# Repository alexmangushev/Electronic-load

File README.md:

# Electronic-load
The project is an electronic load together with a battery capacity meter. The STM32 microcontroller acts as a calculating module.
If you have to use this project, name the folder of project "F103C8_Electronic_load"

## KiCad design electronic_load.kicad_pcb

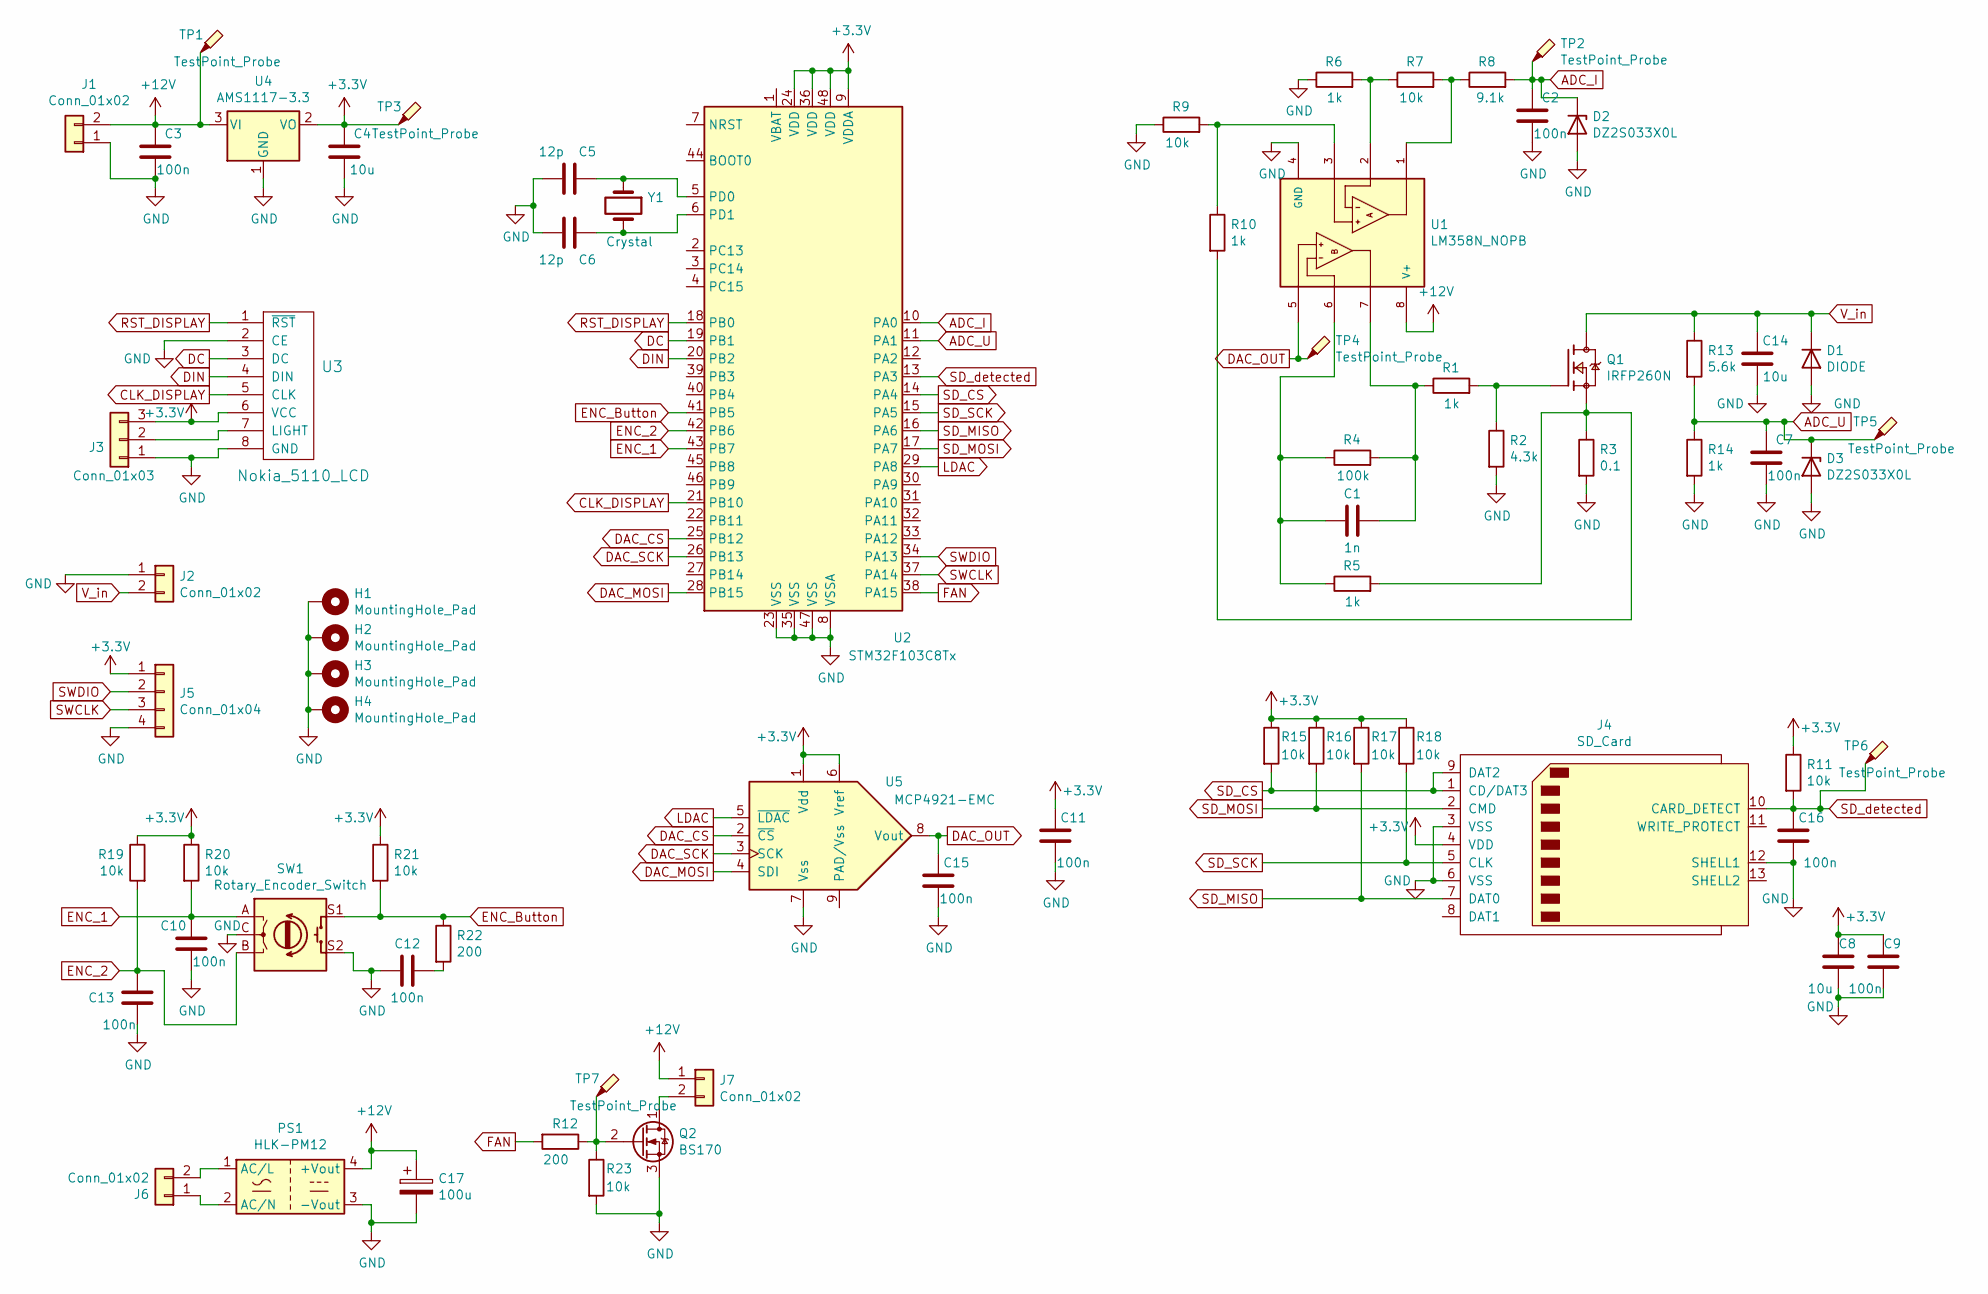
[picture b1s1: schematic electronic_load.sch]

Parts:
C1: 1n; C_1206_3216Metric
C2, C3, C7, C9, C10, C11, C12, C13, C15, C16: 100n; C_1206_3216Metric
C4, C8, C14: 10u; C_1206_3216Metric
C5, C6: 12p; C_1206_3216Metric
C17: 100u; CP_Radial_D7.5mm_P2.50mm
D1: DIODE; D_SMA
D2, D3: DZ2S033X0L; D_SOD-523
H1, H2, H3, H4: MountingHole_Pad; MountingHole_3.2mm_M3_Pad_Via
J1, J6: Conn_01x02; PinHeader_1x02_P2.54mm_Vertical
J2: Conn_01x02; AMASS_XT30UPB-F_1x02_P5.0mm_Vertical
J3: Conn_01x03; PinHeader_1x03_P2.54mm_Vertical
J4: SD_Card; SD_TE_2041021
J5: Conn_01x04; PinHeader_1x04_P2.54mm_Vertical
J7: Conn_01x02; PinSocket_1x02_P2.54mm_Vertical
PS1: HLK-PM12; Hi_Link_12_5
Q1: IRFP260N; TO-247-3_Vertical; PARTREV 08/18/10
Q2: BS170; TO-92_Inline
R1, R5, R6, R10, R14: 1k; R_1206_3216Metric
R2: 4.3k; R_1206_3216Metric
R3: 0.1; R_Axial_Power_L25.0mm_W9.0mm_P27.94mm
R4: 100k; R_1206_3216Metric
R7, R9, R11, R15, R16, R17, R18, R19, R20, R21, R23: 10k; R_1206_3216Metric
R8: 9.1k; R_1206_3216Metric
R12, R22: 200; R_1206_3216Metric
R13: 5.6k; R_1206_3216Metric
SW1: Rotary_Encoder_Switch; RotaryEncoder_Alps_EC11E-Switch_Vertical_H20mm
TP1, TP2, TP3, TP4, TP5, TP6, TP7: TestPoint_Probe; TestPoint_Pad_1.0x1.0mm
U1: LM358N_NOPB; SOIC-8_3.9x4.9mm_P1.27mm
U2: STM32F103C8Tx; LQFP-48_7x7mm_P0.5mm
U3: Nokia_5110_LCD; PinHeader_1x08_P2.54mm_Vertical
U4: AMS1117-3.3; SOT-223-3_TabPin2
U5: MCP4921-EMC; SOIC-8_3.9x4.9mm_P1.27mm
Y1: Crystal; Crystal_SMD_5032-2Pin_5.0x3.2mm

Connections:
+3V3: C4.1, C8.1, C9.1, C11.1, J3.3, J4.4 (VDD), J5.1, R11.1, R15.1, R16.1, R17.1, R18.1, R19.1, R20.1, R21.1, TP3.1, U2.9 (VDDA), U2.24 (VDD), U2.36 (VDD), U2.48 (VDD), U3.6 (VCC), U4.2 (VO), U5.1 (Vdd), U5.6 (Vref)
+12V: C3.1, C17.1, J1.2, J7.1, PS1.4 (+Vout), TP1.1, U1.8 (V+), U4.3 (VI)
ADC_I: C2.1, D2.1 (K), R8.2, TP2.1, U2.10 (PA0)
ADC_U: C7.1, D3.1 (K), R13.2, R14.1, TP5.1, U2.11 (PA1)
CLK_DISPLAY: U2.21 (PB10), U3.5 (CLK)
DAC_CS: U2.25 (PB12), U5.2 (~CS)
DAC_MOSI: U2.28 (PB15), U5.4 (SDI)
DAC_OUT: C15.1, TP4.1, U1.5, U5.8 (Vout)
DAC_SCK: U2.26 (PB13), U5.3 (SCK)
DC: U2.19 (PB1), U3.3 (DC)
DIN: U2.20 (PB2), U3.4 (DIN)
ENC_1: C10.1, R20.2, SW1.A, U2.43 (PB7)
ENC_2: C13.1, R19.2, SW1.B, U2.42 (PB6)
ENC_Button: R21.2, R22.1, SW1.S1, U2.41 (PB5)
FAN: R12.2, U2.38 (PA15)
GND: C2.2, C3.2, C4.2, C5.2, C6.2, C7.2, C8.2, C9.2, C10.2, C11.2, C12.2, C13.2, C14.2, C15.2, C16.2, C17.2, D1.1 (A), D2.2 (A), D3.2 (A), H1.1, H2.1, H3.1, H4.1, J1.1, J2.1, J3.1, J4.3 (VSS), J4.6 (VSS), J4.12 (SHELL1), J5.4, PS1.3 (-Vout), Q2.3 (S), R2.2, R3.2, R6.1, R9.1, R14.2, R23.2, SW1.C, SW1.S2, U1.4 (GND), U2.8 (VSSA), U2.23 (VSS), U2.35 (VSS), U2.47 (VSS), U3.2 (CE), U3.8 (GND), U4.1 (GND), U5.7 (Vss)
LDAC: U2.29 (PA8), U5.5 (~LDAC)
unnamed: C1.1, R1.1, R4.2, U1.7
unnamed: C1.2, R4.1, R5.1, U1.6
unnamed: C5.1, U2.5 (PD0), Y1.1
unnamed: C6.1, U2.6 (PD1), Y1.2
unnamed: C12.1, R22.2
unnamed: J3.2, U3.7 (LIGHT)
unnamed: J6.1, PS1.2 (AC/N)
unnamed: J6.2, PS1.1 (AC/L)
unnamed: J7.2, Q2.1 (D)
unnamed: Q1.1, R1.2, R2.1
unnamed: Q1.3, R3.1, R5.2, R10.2
unnamed: Q2.2 (G), R12.1, R23.1, TP7.1
unnamed: R6.2, R7.1, U1.2
unnamed: R7.2, R8.1, U1.1
unnamed: R9.2, R10.1, U1.3
RST_DISPLAY: U2.18 (PB0), U3.1 (~RST)
SD_CS: J4.1 (CD/DAT3), J4.9 (DAT2), R15.2, U2.14 (PA4)
SD_MISO: J4.7 (DAT0), R17.2, U2.16 (PA6)
SD_MOSI: J4.2 (CMD), R16.2, U2.17 (PA7)
SD_SCK: J4.5 (CLK), R18.2, U2.15 (PA5)
SD_detected: C16.1, J4.10 (CARD_DETECT), R11.2, TP6.1, U2.13 (PA3)
SWCLK: J5.3, U2.37 (PA14)
SWDIO: J5.2, U2.34 (PA13)
V_in: C14.1, D1.2 (K), J2.2, Q1.2, R13.1

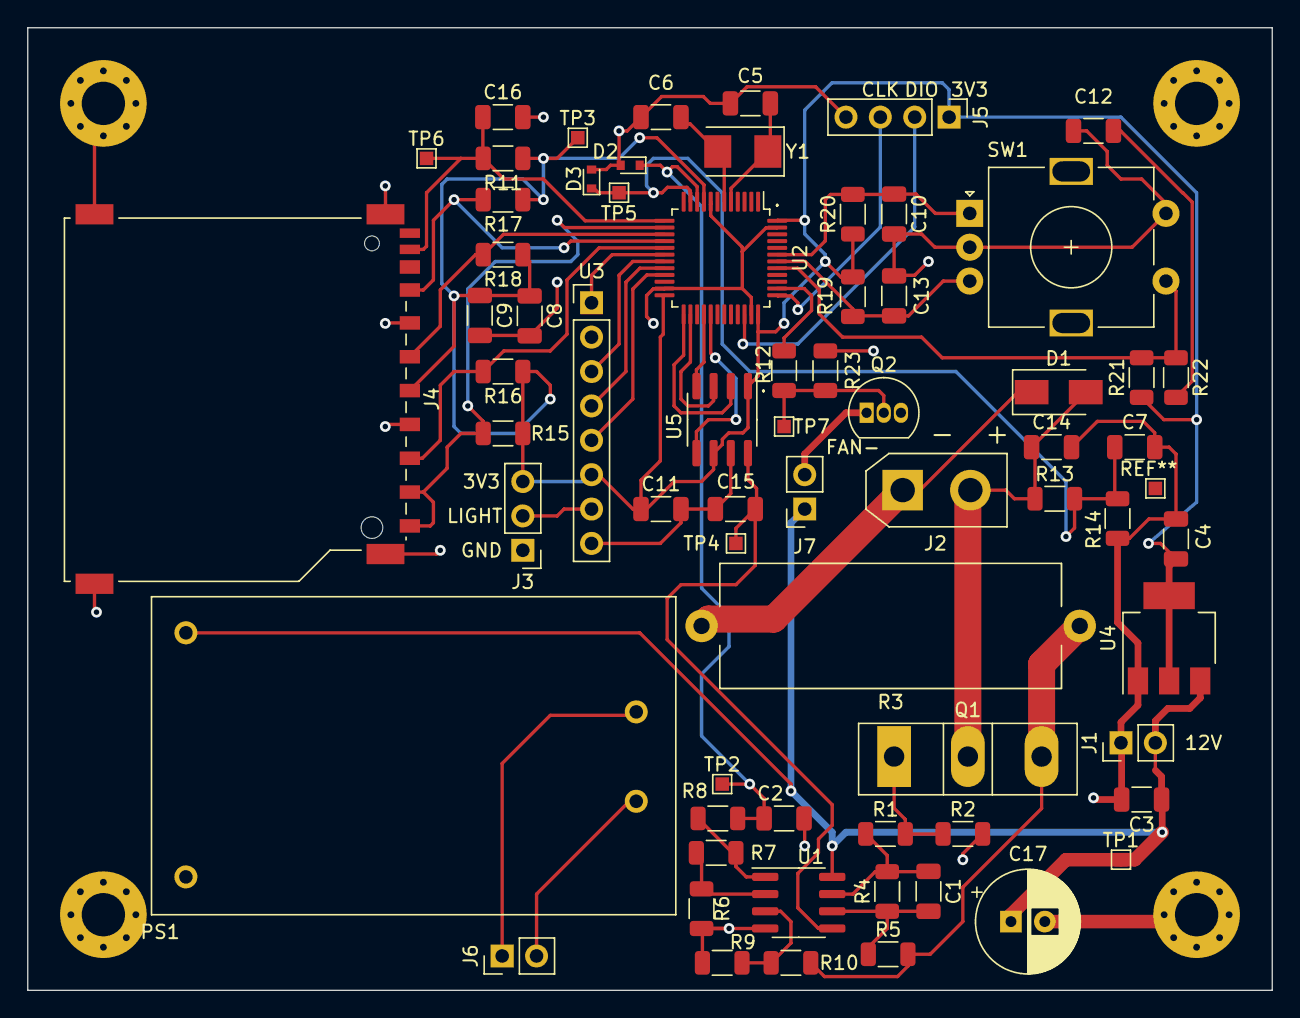
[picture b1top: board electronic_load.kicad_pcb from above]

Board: 2 copper layers, 91.9 x 71.1 mm, 71 parts (0 on the bottom side), 41 nets.

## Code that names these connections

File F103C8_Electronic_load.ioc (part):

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PB10.PinState=GPIO_PIN_SET
PA6.Mode=Full_Duplex_Master
PB10.GPIO_Speed=GPIO_SPEED_FREQ_HIGH
Mcu.UserName=STM32F103C8Tx
PB2.GPIO_Speed=GPIO_SPEED_FREQ_HIGH
PA3.GPIOParameters=GPIO_Label,GPIO_ModeDefaultEXTI
PB0.GPIO_Label=RST
PB13.Signal=SPI2_SCK
PB15.Signal=SPI2_MOSI
RCC.SYSCLKSource=RCC_SYSCLKSOURCE_PLLCLK
PB5.GPIOParameters=GPIO_Label
PD1-OSC_OUT.Signal=RCC_OSC_OUT
PA15.GPIO_Label=FAN
PB0.PinState=GPIO_PIN_SET
PB6.Signal=S_TIM4_CH1
PB12.PinState=GPIO_PIN_SET
PA8.GPIOParameters=PinState,GPIO_Label
PA0-WKUP.GPIOParameters=GPIO_Label
PB2.Signal=GPIO_Output
PB3.Mode=Trace_Asynchronous_SW
PB12.GPIO_Label=SPI_CC
PB0.GPIOParameters=GPIO_Speed,PinState,GPIO_Label
PA1.GPIOParameters=GPIO_Label
PB1.GPIO_Speed=GPIO_SPEED_FREQ_HIGH
PA14.Mode=Trace_Asynchronous_SW
PB14.Mode=Full_Duplex_Master
PB1.GPIO_Label=DC
PB7.Signal=S_TIM4_CH2
PA8.Signal=GPIO_Output
Mcu.Package=LQFP48
PB1.Signal=GPIO_Output
PA6.Signal=SPI1_MISO
PA15.Signal=S_TIM2_CH1_ETR
PB5.GPIO_Label=ENC_Button
PB10.GPIOParameters=GPIO_Speed,PinState,GPIO_Label
PB13.Mode=Full_Duplex_Master
PA4.GPIO_Label=SD_CS
PA8.PinState=GPIO_PIN_SET
PA3.Signal=GPXTI3
PA5.Mode=Full_Duplex_Master
PA7.Mode=Full_Duplex_Master
PD1-OSC_OUT.Mode=HSE-External-Oscillator
PA15.GPIOParameters=GPIO_Label
PD0-OSC_IN.Signal=RCC_OSC_IN
PA0-WKUP.GPIO_Label=I
PA0-WKUP.Signal=ADCx_IN0
PA3.GPIO_ModeDefaultEXTI=GPIO_MODE_IT_RISING_FALLING
PB0.GPIO_Speed=GPIO_SPEED_FREQ_HIGH
PA13.Signal=SYS_JTMS-SWDIO
PA8.GPIO_Label=LDAC 
PB10.GPIO_Label=CLK
PB2.GPIOParameters=GPIO_Speed,GPIO_Label
PA1.Signal=ADCx_IN1
PB12.GPIO_Speed=GPIO_SPEED_FREQ_HIGH
PD0-OSC_IN.Mode=HSE-External-Oscillator
PB10.Signal=GPIO_Output
PB14.Signal=SPI2_MISO
PA5.Signal=SPI1_SCK
board=custom
PB15.Mode=Full_Duplex_Master
PA1.GPIO_Label=U
PA4.GPIOParameters=GPIO_Label
PA13.Mode=Trace_Asynchronous_SW
Mcu.Name=STM32F103C(8-B)Tx
PB3.Signal=SYS_JTDO-TRACESWO
PA4.Signal=GPIO_Output
RCC.SYSCLKFreq_VALUE=64000000
PB5.Signal=GPXTI5
RCC.HSEDivPLL=RCC_HSE_PREDIV_DIV2
PA14.Signal=SYS_JTCK-SWCLK
PB2.GPIO_Label=DIN
PB0.Signal=GPIO_Output
PB12.GPIOParameters=GPIO_Speed,PinState,GPIO_Label
PB12.Signal=GPIO_Output
PA3.GPIO_Label=SD_detected
PB1.GPIOParameters=GPIO_Speed,GPIO_Label
PA7.Signal=SPI1_MOSI

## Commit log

2021-11-07 make stabilaze without DMA and SD
2021-11-08 make stabilization with DMA and partially SD
2021-11-08 add README
2021-11-09 Schematics with PCB and components from LCSC
2021-11-13 some fix
2021-11-16 stabilaze with DMA and SD
2021-12-02 add work with sd_sc
2021-12-02 work with both SD (SC and HC)
